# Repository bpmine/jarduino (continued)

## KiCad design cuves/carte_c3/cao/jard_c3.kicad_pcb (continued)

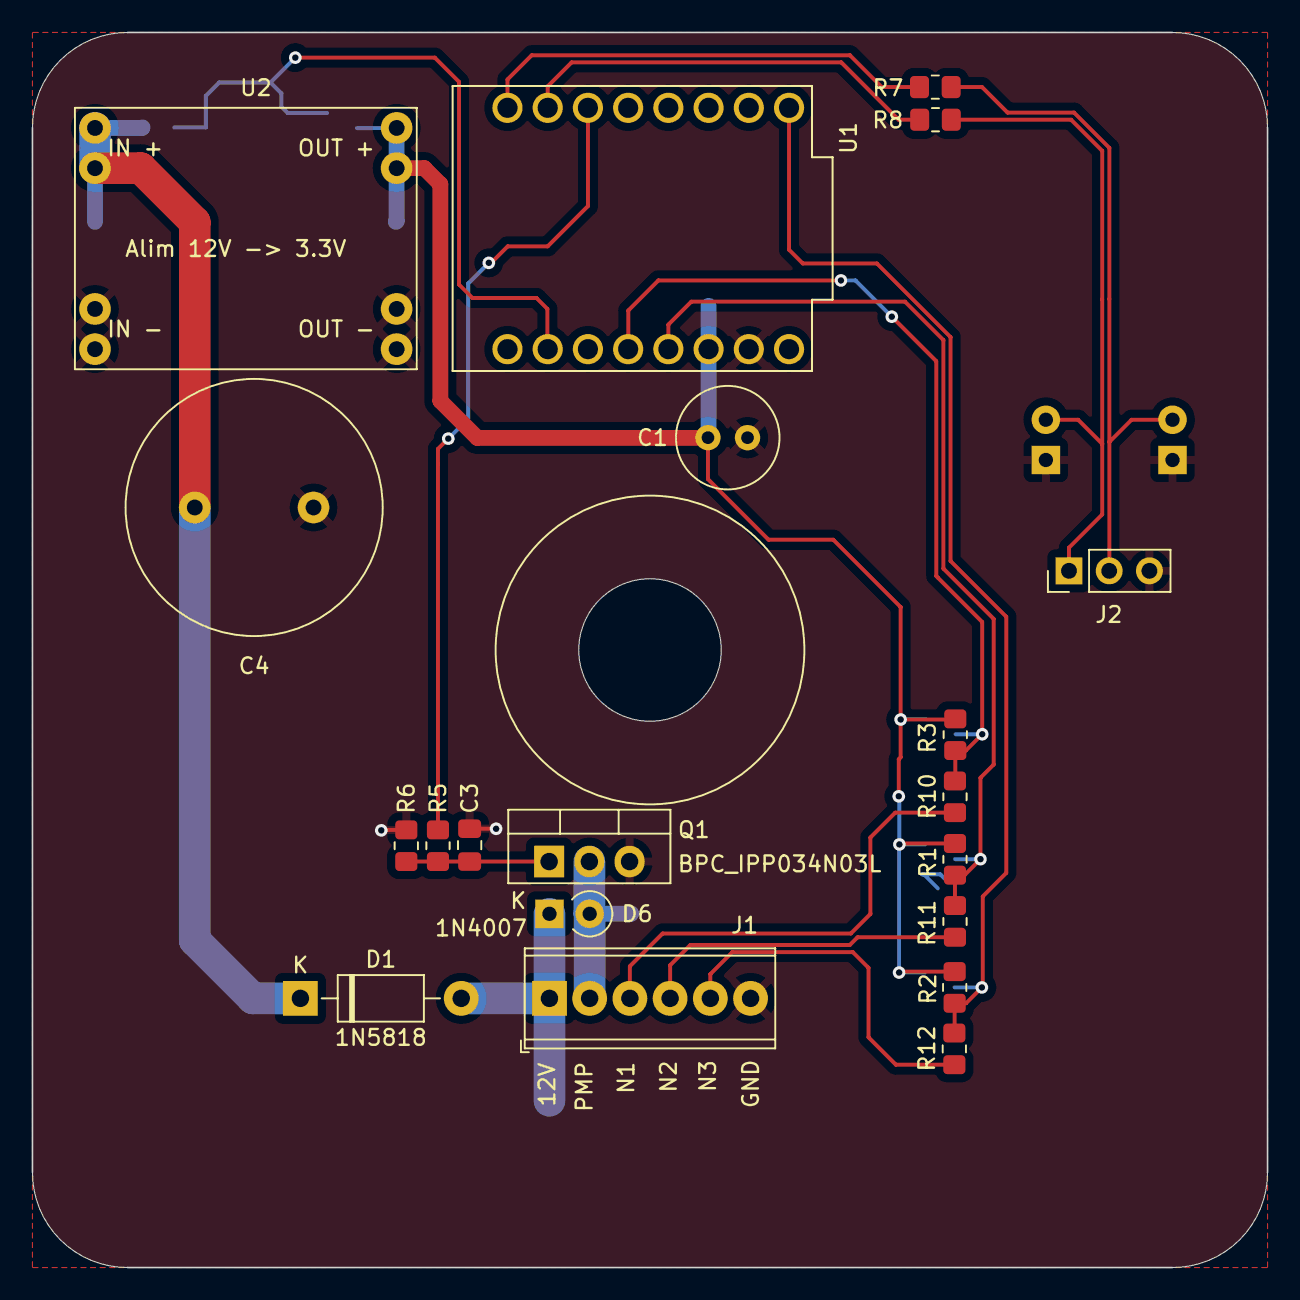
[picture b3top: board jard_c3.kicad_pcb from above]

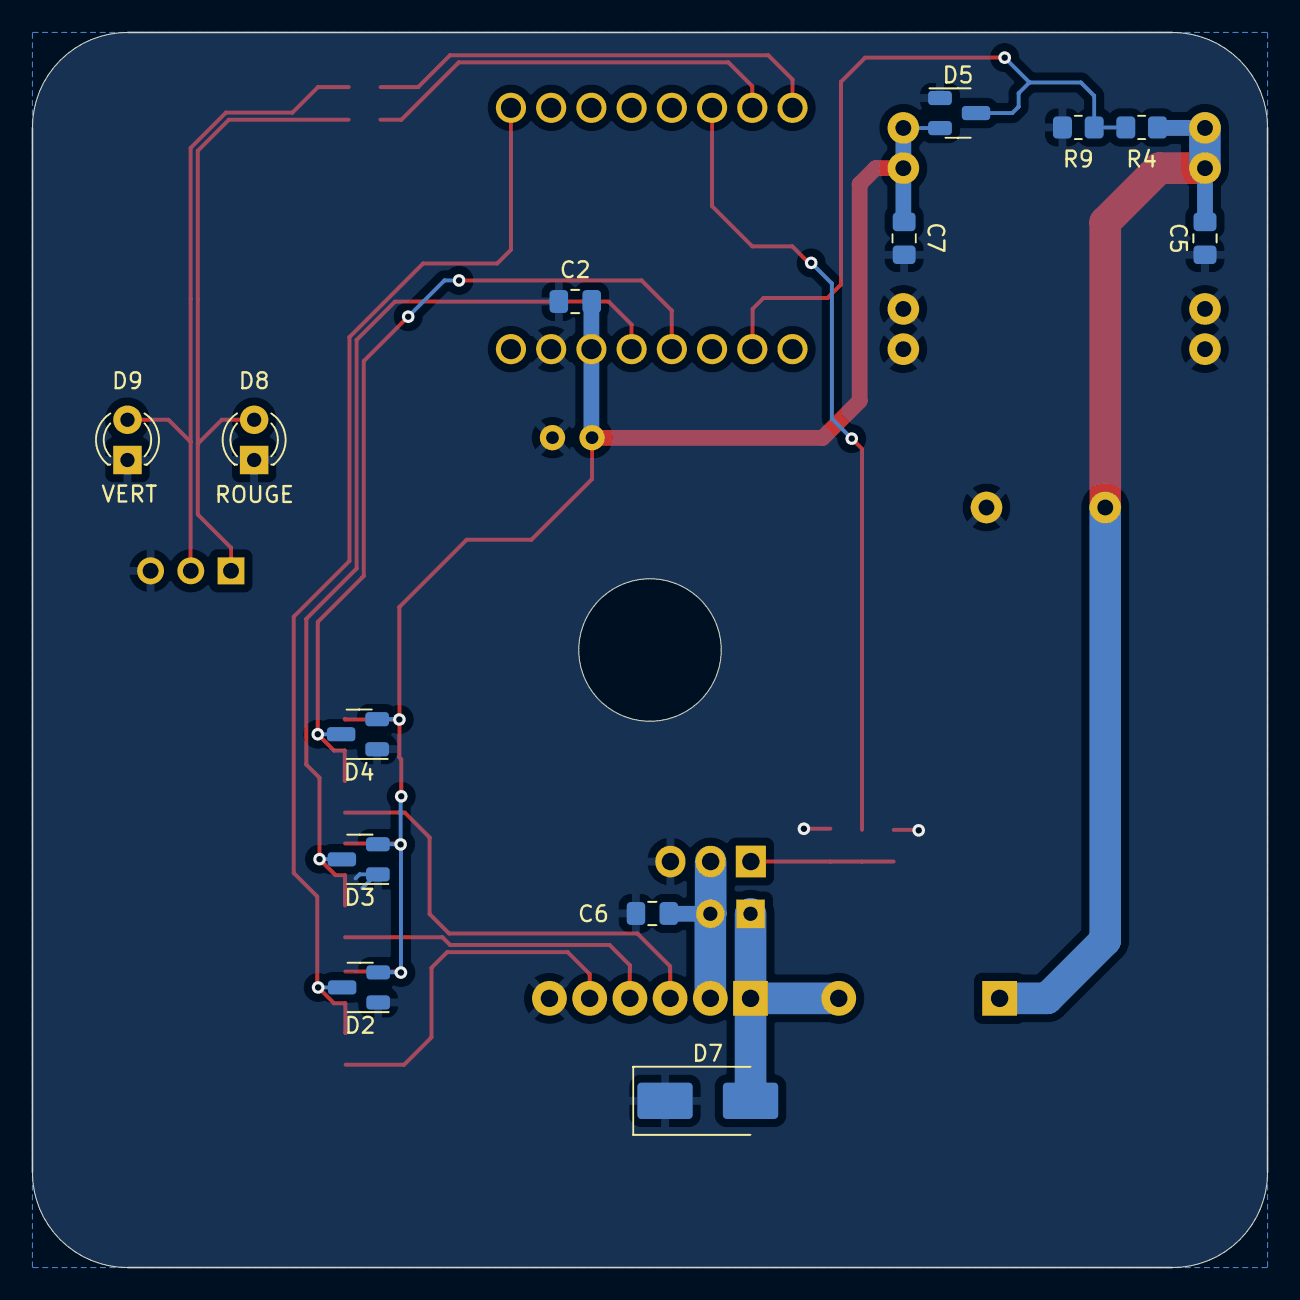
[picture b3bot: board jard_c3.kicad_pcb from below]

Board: 2 copper layers, 78.0 x 78.0 mm, 33 parts (13 on the bottom side), 18 nets.

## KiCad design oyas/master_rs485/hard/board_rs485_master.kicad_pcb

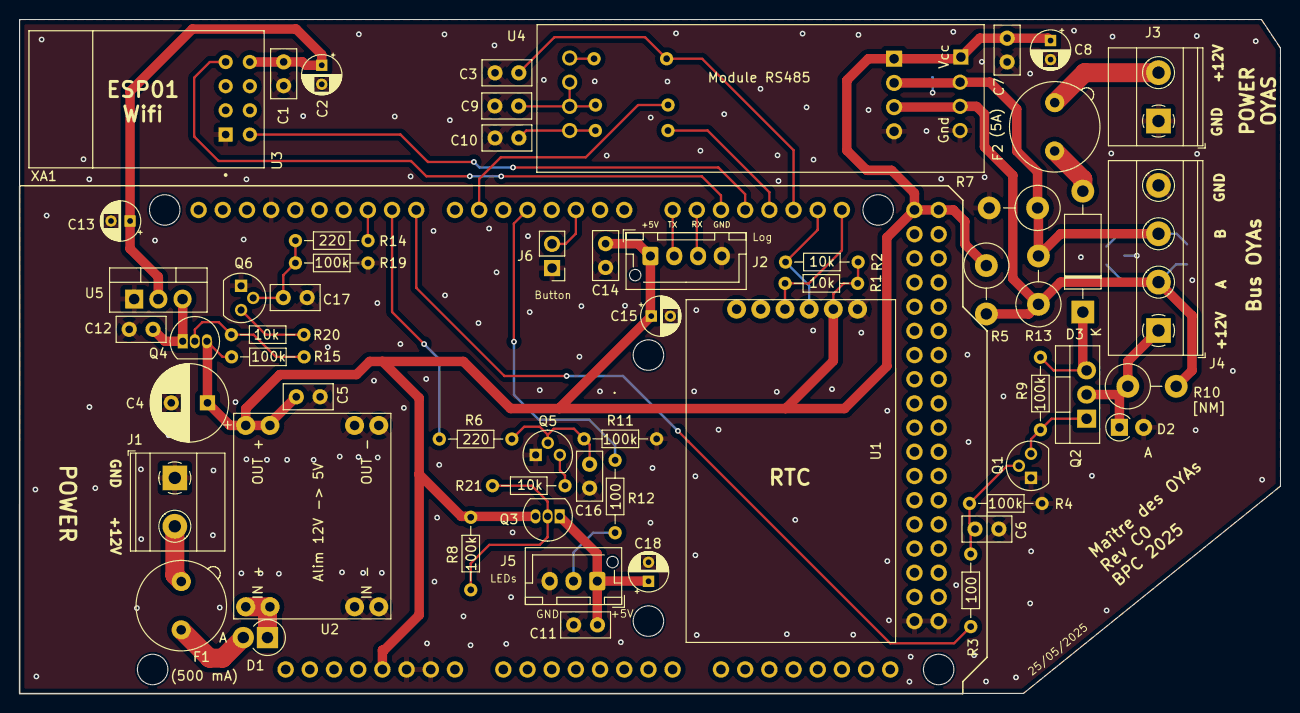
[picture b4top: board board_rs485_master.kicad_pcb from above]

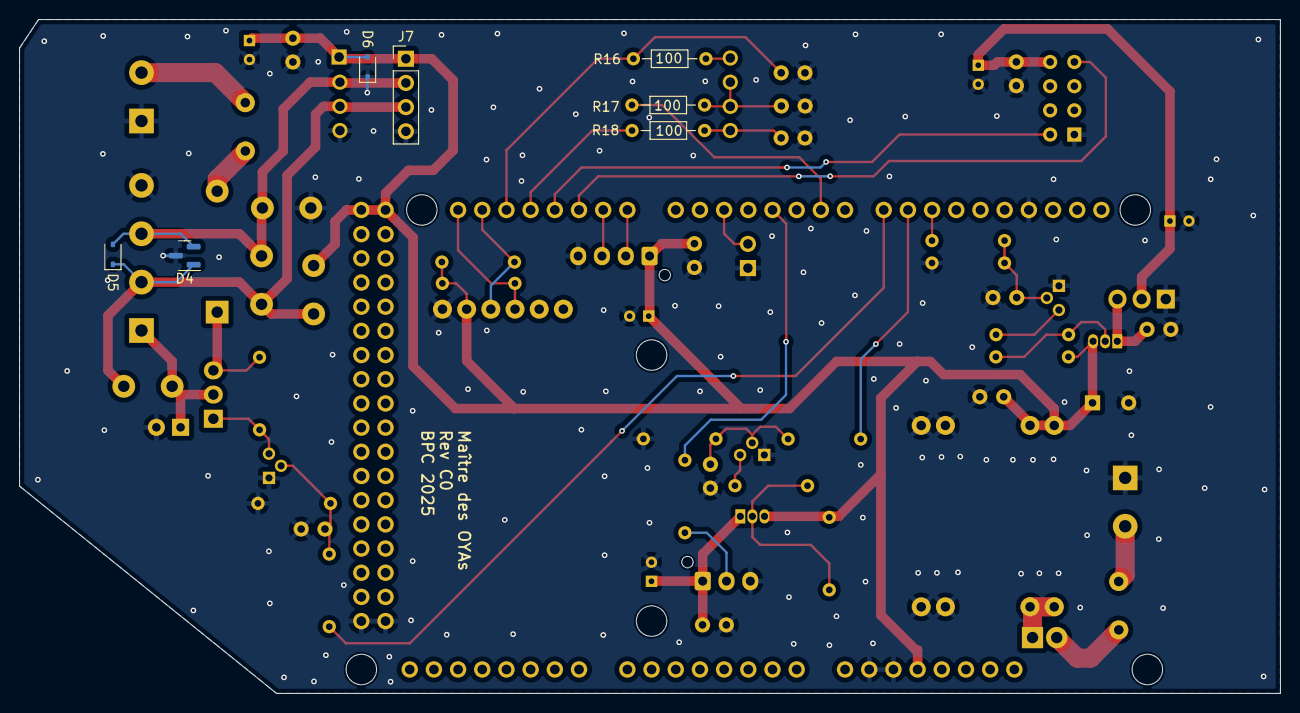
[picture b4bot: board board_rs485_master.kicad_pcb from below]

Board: 2 copper layers, 132.4 x 70.8 mm, 66 parts (7 on the bottom side), 40 nets.

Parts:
C1, C5, C6, C7, C11, C12, C14, C16, C17: 100nF; C_Disc_D5.0mm_W2.5mm_P2.50mm
C2, C8, C13, C15, C18: 10µF; CP_Radial_D4.0mm_P2.00mm
C3, C9, C10: 1nF; C_Disc_D5.0mm_W2.5mm_P2.50mm
C4: 100µF; CP_Radial_D8.0mm_P3.80mm
D1: SR560; D_DO-15_P2.54mm_Vertical_AnodeUp
D2: BAT42; D_A-405_P2.54mm_Vertical_AnodeUp
D3: SR560; D_DO-15_P12.70mm_Horizontal
D4: SM712_SOT23; SOT-23
D5, D6: SD12_SOD323; D_SOD-323
F1: 500 mA; Fuseholder_TR5_Littelfuse_No560_No460
F2: 5A; Fuseholder_TR5_Littelfuse_No560_No460
J1: POWER_12V; TerminalBlock_Phoenix_MKDS-1,5-2-5.08_1x02_P5.08mm_Horizont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
J2: Log; JST_XH_B4B-XH-AM_1x04_P2.50mm_Vertical
J3: POWER_OYAS_12V; TerminalBlock_Phoenix_MKDS-1,5-2-5.08_1x02_P5.08mm_Horizont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
J4: BUS_OYAS; TerminalBlock_Phoenix_MKDS-1,5-4-5.08_1x04_P5.08mm_Horizont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
J5: Leds RGB; JST_XH_B3B-XH-AM_1x03_P2.50mm_Vertical
J6: Button; PinHeader_1x02_P2.54mm_Vertical
J7: Adapt BUS; PinHeader_1x04_P2.54mm_Vertical
Q1, Q5, Q6: BPC_2N2222A; TO-92
Q2: P03P4L-04; TO-220-3_Vertical
Q3, Q4: BC327; TO-92_Inline
R1, R2, R20, R21: 10k; R_Axial_DIN0204_L3.6mm_D1.6mm_P7.62mm_Horizontal
R3, R12, R16, R17, R18: 100; R_Axial_DIN0204_L3.6mm_D1.6mm_P7.62mm_Horizontal
R4, R8, R9, R11, R15, R19: 100k; R_Axial_DIN0204_L3.6mm_D1.6mm_P7.62mm_Horizontal
R5, R7: 220; R_Axial_DIN0414_L11.9mm_D4.5mm_P5.08mm_Vertical
R6, R14: 220; R_Axial_DIN0204_L3.6mm_D1.6mm_P7.62mm_Horizontal
R10: R; R_Axial_DIN0414_L11.9mm_D4.5mm_P5.08mm_Vertical
R13: 128; R_Axial_DIN0414_L11.9mm_D4.5mm_P5.08mm_Vertical
U1: RtcArduino; BPC_RtcArduino
U2: BPC_Alim5V
U3: BPC_ESP8266-01_ESP-01; BPC_XCVR_ESP8266-01_ESP-01
U4: BPC_Mod485
U5: LM1117DT-3.3; TO-220-3_Vertical
XA1: Arduino_Mega2560_Shield; BPC_Arduino_Mega2560_Shield

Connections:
+5V: C4.1, C5.1, C7.1, C8.1, C14.1, C15.1, D6.2 (A2), J2.1, J7.1, Q3.3 (E), Q4.3 (E), R1.1, R2.1, R5.1, R8.1, R15.1, U1.2 (VCC), U2.7 (OUT+), U2.8 (OUT+), U4.1 (Vcc), XA1.5V1 (5V), XA1.5V3 (5V), XA1.5V4 (5V)
A: D4.1 (A1), D5.1 (A1), J4.2, J7.3, R5.2, R10.2, R13.1, U4.3 (A)
B: D4.2 (A2), D5.2 (A2), J4.3, J7.2, R7.1, R13.2, U4.2 (B)
CMD_LEDS_PWR: R6.1, XA1.D9
CMD_OYAS_PWR: R3.2, XA1.D8
CMD_WIFI_PWR: R14.1, XA1.D10
DATA_LEDS: R12.1, XA1.D4
GND: C1.2, C2.2, C3.2, C4.2, C5.2, C6.2, C7.2, C8.2, C9.2, C10.2, C11.2, C12.2, C13.2, C14.2, C15.2, C16.2, C17.2, C18.2, D2.2 (A), D4.3 (common), D6.1 (A1), J1.1, J2.4, J3.1, J4.4, J5.3, J6.1, J7.4, Q1.1, Q5.1, Q6.1, R4.2, R7.2, R11.2, R19.2, U1.1 (GND), U2.3 (IN-), U2.4 (IN-), U2.5 (OUT-), U2.6 (OUT-), U3.1 (GND), U4.4 (Gnd), U5.1 (GND), XA1.GND1 (GND), XA1.GND2 (GND), XA1.GND3 (GND), XA1.GND5 (GND), XA1.GND6 (GND)
unnamed: C6.1, Q1.2, R3.1, R4.1
unnamed: C16.1, Q5.2, R6.2, R11.1
unnamed: C17.1, Q6.2, R14.2, R19.1
unnamed: D1.2 (A), F1.1
unnamed: D1.1 (K), U2.1 (IN+), U2.2 (IN+)
unnamed: D2.1 (K), J4.1, Q2.2 (D), R10.1
unnamed: D3.2 (A), F2.1
unnamed: D3.1 (K), Q2.3 (S), R9.1
unnamed: F1.2, J1.2
unnamed: F2.2, J3.2
unnamed: C11.1, C18.1, J5.1, Q3.1 (C)
unnamed: J5.2, R12.2
unnamed: Q1.3, Q2.1 (G), R9.2
unnamed: Q3.2 (B), R8.2, R21.2
unnamed: Q4.2 (B), R15.2, R20.2
unnamed: C12.1, Q4.1 (C), U5.3 (VI)
unnamed: Q5.3, R21.1
unnamed: Q6.3, R20.1
unnamed: C9.1, R17.1, U4.6 (DE), U4.7 (RE)
unnamed: C10.1, R18.1, U4.5 (DI)
unnamed: R16.1, U4.8 (RO)
POWER_3.3: C1.1, C2.1, C13.1, U3.8 (VCC), U5.2 (VO)
RS485_RX: C3.1, R16.2, XA1.D19 (D19_RX1)
RS485_TX: R18.2, XA1.D18 (D18_TX1)
RX_LOG: J2.3, XA1.D15 (D15_RX3)
RX_WIFI: U3.5 (TXD), XA1.D17 (D17_RX2)
SCL: R1.2, U1.4 (SCL), XA1.D21 (D21_SCL)
SDA: R2.2, U1.3 (SDA), XA1.D20 (D20_SDA)
TEST_BTN: J6.2, XA1.D2 (D2_INT0)
TX_EN: R17.2, XA1.D6
TX_LOG: J2.2, XA1.D14 (D14_TX3)
TX_WIFI: U3.4 (RXD), XA1.D16 (D16_TX2)

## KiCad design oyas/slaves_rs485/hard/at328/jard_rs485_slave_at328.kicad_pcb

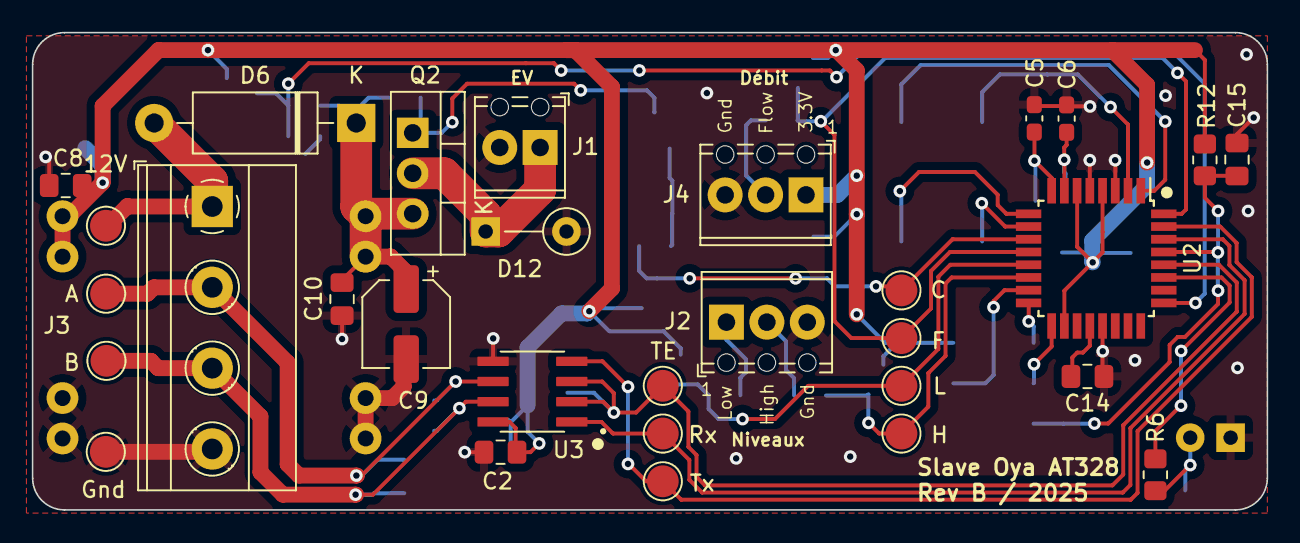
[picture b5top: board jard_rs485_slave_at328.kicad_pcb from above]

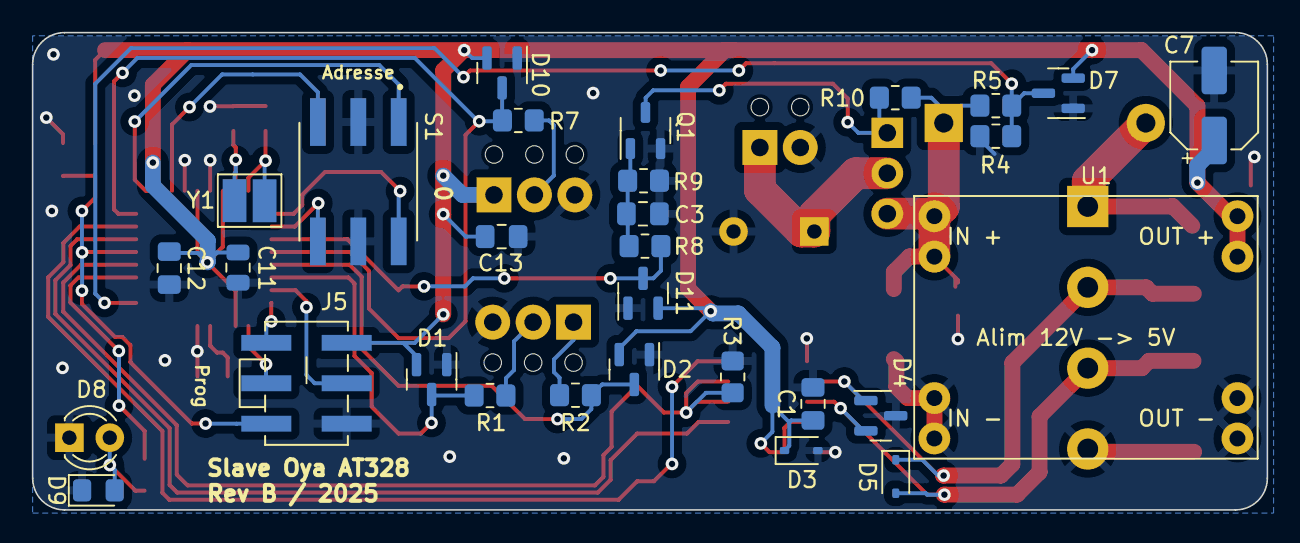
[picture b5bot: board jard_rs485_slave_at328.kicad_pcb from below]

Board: 2 copper layers, 77.6 x 30.0 mm, 60 parts (30 on the bottom side), 33 nets.

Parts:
C1: 10nF; C_0805_2012Metric_Pad1.18x1.45mm_HandSolder
C2, C3, C12, C13, C14, C15: 100nF; C_0805_2012Metric_Pad1.18x1.45mm_HandSolder
C5, C6: 6pF; C_0603_1608Metric_Pad1.08x0.95mm_HandSolder
C7, C9: 10µF; CP_Elec_5x5.9
C8, C10: 1nF; C_0805_2012Metric_Pad1.18x1.45mm_HandSolder
C11: 1nF; C_0805_2012Metric
D1, D2, D7, D10, D11: BAV99; SOT-23
D3, D5: SD12_SOD323; D_SOD-323
D4: SM712_SOT23; SOT-23
D6: SR560; D_DO-15_P12.70mm_Horizontal
D8: LED; LED_D3.0mm_FlatTop
D9: LED; LED_0805_2012Metric_Pad1.15x1.40mm_HandSolder
D12: 1N4007G; D_A-405_P5.08mm_Vertical_KathodeUp
J1: EV1; TerminalBlock_Phoenix_MPT-0,5-2-2.54_1x02_P2.54mm_Horizontal
J2: Niveaux; TerminalBlock_Phoenix_MPT-0,5-3-2.54_1x03_P2.54mm_Horizontal
J3: POWER; TerminalBlock_Phoenix_MKDS-1,5-4-5.08_1x04_P5.08mm_Horizont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
J4: Débit; TerminalBlock_Phoenix_MPT-0,5-3-2.54_1x03_P2.54mm_Horizontal
J5: ISCP; BPC_ISCP_CMS
Q1: BPC_FMMT38C; BPC_SOT-23-3
Q2: P03P4L-04; TO-220-3_Vertical
R1, R2, R7, R12: 100; R_0805_2012Metric_Pad1.20x1.40mm_HandSolder
R3, R5, R9, R10: 100k; R_0805_2012Metric_Pad1.20x1.40mm_HandSolder
R4: 40k; R_0805_2012Metric_Pad1.20x1.40mm_HandSolder
R6, R8: 220; R_0805_2012Metric_Pad1.20x1.40mm_HandSolder
S1: RDS-16S-74385-SMT; BPC_RDS-16S-74385-SMT
TP1: H; TestPoint_Pad_D2.0mm
TP2: L; TestPoint_Pad_D2.0mm
TP3: Rx; TestPoint_Pad_D2.0mm
TP4: Tx; TestPoint_Pad_D2.0mm
TP5: TE; TestPoint_Pad_D2.0mm
TP6: B; TestPoint_Pad_D2.0mm
TP7: A; TestPoint_Pad_D2.0mm
TP8: 12V; TestPoint_Pad_D2.0mm
TP9: Gnd; TestPoint_Pad_D2.0mm
TP10: F; TestPoint_Pad_D2.0mm
TP11: C; TestPoint_Pad_D2.0mm
U1: BPC_Alim5V
U2: ATmega328P-A; TQFP-32_7x7mm_P0.8mm
U3: MAX485E; BPC_MAX485E_SOIC127P600X175-8N
Y1: 8MHz; BPC_Quartz_8MHz

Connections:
+5V: C1.1, C2.2, C7.1, C8.1, C11.1, C12.1, C13.1, D1.2 (A), D2.2 (A), D3.1 (A1), D7.2 (A), D10.2 (A), D11.2 (A), J4.1, J5.2 (VCC), R12.2, U1.7 (OUT+), U1.8 (OUT+), U2.4 (VCC), U2.6 (VCC), U2.18 (AVCC), U3.8 (VCC)
A1: S1.1, U2.1 (PD3)
A2: S1.2, U2.10 (PD6)
A3: S1.4, U2.2 (PD4)
A4: S1.8, U2.9 (PD5)
BUS_A: D4.1 (A1), D5.1 (A1), J3.2, TP7.1, U3.6 (A)
BUS_B: D4.2 (A2), D5.2 (A2), J3.3, TP6.1, U3.7 (B)
CMD_EV1: D11.3 (K), R8.1, TP11.1, U2.11 (PD7)
FLOW: D10.3 (K), R7.2, TP10.1, U2.12 (PB0), U2.32 (PD2)
GND: C1.2, C2.1, C3.2, C5.2, C6.1, C7.2, C8.2, C9.2, C10.2, C11.2, C12.2, C13.2, C14.1, C15.2, D1.1 (K), D2.1 (K), D3.2 (A2), D4.3 (common), D7.1 (K), D8.1 (K), D9.1 (K), D10.1 (K), D11.1 (K), D12.2 (A), J1.2, J2.3, J3.4, J4.3, J5.6 (GND), Q1.2 (E), R3.2, R4.1, R9.2, S1.C_1 (C), S1.C_2 (C), TP9.1, U1.3 (IN-), U1.4 (IN-), U1.5 (OUT-), U1.6 (OUT-), U2.3 (GND), U2.5 (GND), U2.21 (GND), U3.5 (GND)
LED: R6.1, U2.27 (PC4)
LVL_HIGH: D1.3 (K), R1.2, TP1.1, U2.14 (PB2)
LVL_LOW: D2.3 (K), R2.2, TP2.1, U2.13 (PB1)
MISO: J5.1 (MISO), U2.16 (PB4)
MOSI: J5.4 (MOSI), U2.15 (PB3)
unnamed: D6.2 (A), J3.1, TP8.1
unnamed: D8.2 (A), D9.2 (A), R6.2
unnamed: D12.1 (K), J1.1, Q2.2 (D)
unnamed: J2.1, R2.1
unnamed: J2.2, R1.1
unnamed: J4.2, R7.1
unnamed: C3.1, Q1.1 (B), R8.2, R9.1
unnamed: Q1.3 (C), Q2.1 (G), R10.2
unnamed: C14.2, U2.20 (AREF)
unnamed: C6.2, U2.7 (XTAL1/PB6), Y1.2
unnamed: C5.1, U2.8 (XTAL2/PB7), Y1.1
POWER_12V: C9.1, C10.1, D6.1 (K), Q2.3 (S), R5.2, R10.1, U1.1 (IN+), U1.2 (IN+)
POW_MES: D7.3 (K), R4.2, R5.1, U2.25 (PC2)
RESET: C15.1, J5.5 (RST), R12.1, U2.29 (~RESET/PC6)
RX: TP3.1, U2.30 (PD0), U3.1 (RO)
SCK: J5.3 (SCK), U2.17 (PB5)
TX: TP4.1, U2.31 (PD1), U3.4 (DI)
TX_EN: R3.1, TP5.1, U2.28 (PC5), U3.2 (~RE), U3.3 (DE)

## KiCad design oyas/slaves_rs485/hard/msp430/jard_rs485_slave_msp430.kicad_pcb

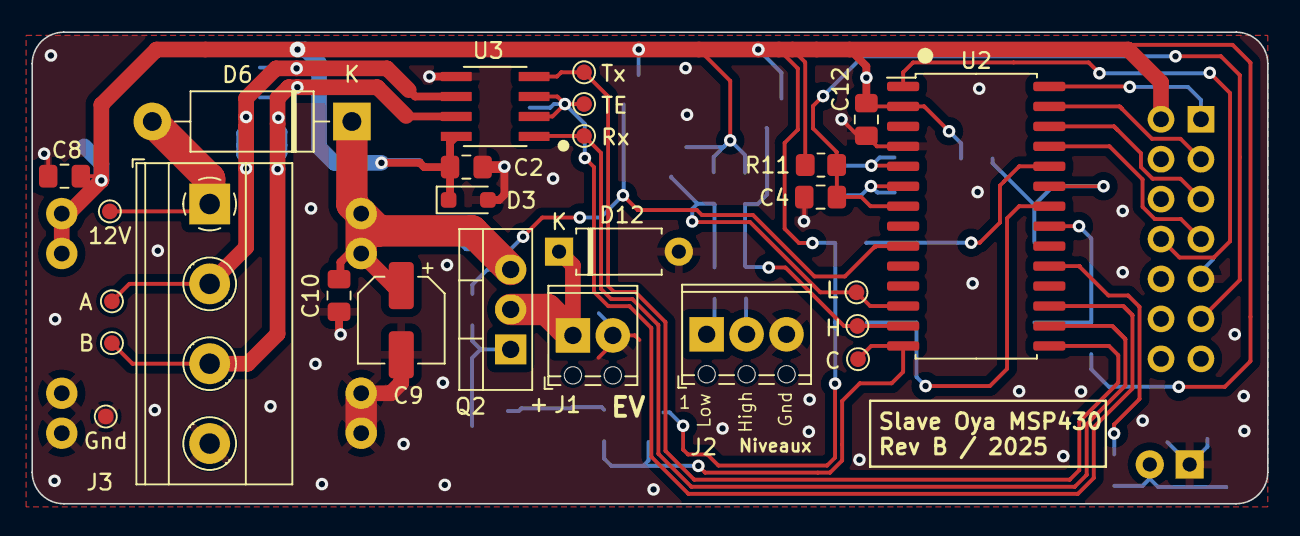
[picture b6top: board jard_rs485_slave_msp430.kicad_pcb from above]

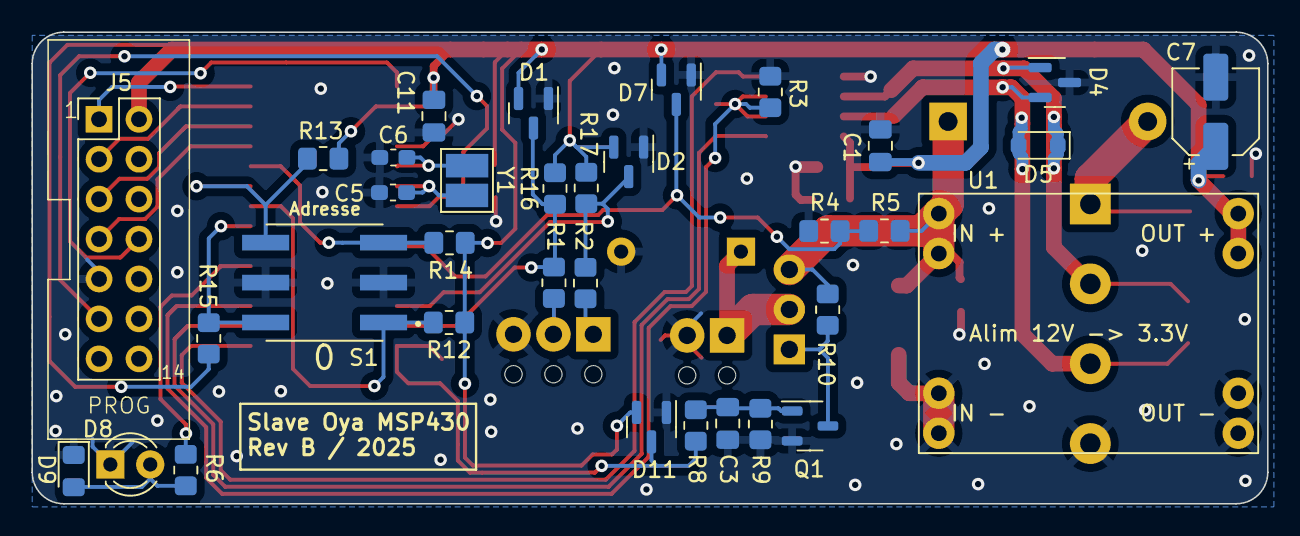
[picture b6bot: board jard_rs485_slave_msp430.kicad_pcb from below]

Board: 2 copper layers, 78.6 x 30.0 mm, 60 parts (34 on the bottom side), 32 nets.

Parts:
C1: 10µF; C_0805_2012Metric_Pad1.18x1.45mm_HandSolder
C2, C3, C12: 100nF; C_0805_2012Metric_Pad1.18x1.45mm_HandSolder
C4, C8, C10, C11: 1nF; C_0805_2012Metric_Pad1.18x1.45mm_HandSolder
C5, C6: 10pF; C_0603_1608Metric_Pad1.08x0.95mm_HandSolder
C7, C9: 10µF; CP_Elec_5x5.9
D1, D2, D7, D11: BAV99; SOT-23
D3, D5: SD12_SOD323; BPC_D_SOD-323_HandSoldering
D4: SM712_SOT23; SOT-23
D6: SR560; D_DO-15_P12.70mm_Horizontal
D8: LED; LED_D3.0mm_FlatTop
D9: LED; LED_0805_2012Metric_Pad1.15x1.40mm_HandSolder
D12: 1N4007G; D_A-405_P7.62mm_Horizontal
J1: EV1; TerminalBlock_Phoenix_MPT-0,5-2-2.54_1x02_P2.54mm_Horizontal
J2: Niveaux; TerminalBlock_Phoenix_MPT-0,5-3-2.54_1x03_P2.54mm_Horizontal
J3: POWER; TerminalBlock_Phoenix_MKDS-1,5-4-5.08_1x04_P5.08mm_Horizont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
J5: Prog MSP; BPC_PROG_MSP
Q1: BPC_FMMT38C; BPC_SOT-23-3
Q2: P03P4L-04; TO-220-3_Vertical
R1, R2: 100; R_0805_2012Metric_Pad1.20x1.40mm_HandSolder
R3, R5, R9, R10, R11, R12, R13, R14, R15, R16, R17: 100k; R_0805_2012Metric_Pad1.20x1.40mm_HandSolder
R4: 40k; R_0805_2012Metric_Pad1.20x1.40mm_HandSolder
R6, R8: 220; R_0805_2012Metric_Pad1.20x1.40mm_HandSolder
S1: RDS-16S-74385-SMT; BPC_RDS-16S-74385-SMT
TP1: H; TestPoint_Pad_D1.0mm
TP2: L; TestPoint_Pad_D1.0mm
TP3: Rx; TestPoint_Pad_D1.0mm
TP4: Tx; TestPoint_Pad_D1.0mm
TP5: TE; TestPoint_Pad_D1.0mm
TP6: B; TestPoint_Pad_D1.0mm
TP7: A; TestPoint_Pad_D1.0mm
TP8: 12V; TestPoint_Pad_D1.0mm
TP9: Gnd; TestPoint_Pad_D1.0mm
TP11: C; TestPoint_Pad_D1.0mm
U1: BPC_Alim3_3V
U2: MSP430F1232IDW; SOIC-28W_7.5x17.9mm_P1.27mm
U3: MAX485E; BPC_MAX485E_SOIC127P600X175-8N
Y1: 8MHz; BPC_Quartz_8MHz

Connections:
+3.3V: C1.1, C2.2, C7.1, C8.1, C11.2, C12.2, D1.2 (A), D2.2 (A), D3.1 (A1), D7.2 (A), D11.2 (A), J5.2 (Vcc), R11.2, R12.2, R13.2, R14.2, R15.2, R16.2, R17.2, U1.7 (OUT+), U1.8 (OUT+), U2.2 (VCC), U3.8 (VCC)
A1: R12.1, S1.1, U2.22 (TA0/P1.1)
A2: R13.1, S1.2, U2.23 (TA1/P1.2)
A3: R14.1, S1.4, U2.24 (TA2/P1.3)
A4: R15.1, S1.8, U2.21 (TACLK/ADC10CLK/P1.0)
BUS_A: D4.1 (A1), D5.1 (A1), J3.2, TP7.1, U3.6 (A)
BUS_B: D4.2 (A2), D5.2 (A2), J3.3, TP6.1, U3.7 (B)
CMD_EV1: D11.3 (K), R8.1, TP11.1, U2.14 (P3.3/UCLK0)
GND: C1.2, C2.1, C3.2, C4.2, C5.1, C6.1, C7.2, C8.2, C9.2, C10.2, C11.1, C12.1, D1.1 (K), D2.1 (K), D3.2 (A2), D4.3 (common), D7.1 (K), D8.1 (K), D9.1 (K), D11.1 (K), D12.2 (A), J1.2, J2.3, J3.4, J5.9 (GND), Q1.2 (E), R3.2, R4.1, R9.2, S1.C_1 (C), S1.C_2 (C), TP9.1, U1.3 (IN-), U1.4 (IN-), U1.5 (OUT-), U1.6 (OUT-), U2.4 (VSS), U3.5 (GND)
LED: R6.1, U2.19 (TA1/VeREF-/VREF-/A3/P2.3)
LVL_HIGH: D1.3 (K), R1.2, R16.1, TP1.1, U2.13 (P3.2/SOMI0)
LVL_LOW: D2.3 (K), R2.2, R17.1, TP2.1, U2.12 (P3.1/SIMO0)
unnamed: D6.2 (A), J3.1, TP8.1
unnamed: D8.2 (A), D9.2 (A), R6.2
unnamed: D12.1 (K), J1.1, Q2.2 (D)
unnamed: J2.1, R2.1
unnamed: J2.2, R1.1
unnamed: C4.1, J5.11 (RST), R11.1, U2.7 (~RST/NMI)
unnamed: C3.1, Q1.1 (B), R8.2, R9.1
unnamed: Q1.3 (C), Q2.1 (G), R10.2
unnamed: C5.2, U2.6 (XIN), Y1.2
unnamed: C6.2, U2.5 (XOUT), Y1.1
POWER_12V: C9.1, C10.1, D6.1 (K), Q2.3 (S), R5.2, R10.1, U1.1 (IN+), U1.2 (IN+)
POW_MES: D7.3 (K), R4.2, R5.1, U2.9 (INCLK/A1/P2.1)
RX: TP3.1, U2.16 (P3.5/URXD0), U3.1 (RO)
TCK: J5.7 (TCK), U2.25 (SMCLK/TCK/P1.4)
TDI: J5.3 (TDI), U2.27 (TDI/TCLK/TA1/P1.6)
TDO: J5.1 (TDO), U2.28 (TDO/TDI/TA2/P1.7)
TEST: J5.8 (TEST), U2.1 (TEST)
TMS: J5.5 (TMS), U2.26 (TMS/TA0/P1.5)
TX: TP4.1, U2.15 (P3.4/UTXD0), U3.4 (DI)
TX_EN: R3.1, TP5.1, U2.17 (P3.6/A6), U3.2 (~RE), U3.3 (DE)

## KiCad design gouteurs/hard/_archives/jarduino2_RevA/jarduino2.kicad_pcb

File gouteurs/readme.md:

# Goutteurs (Jarduino2)

Jarduino2 est une évolution du premier jarduino fabriqué en 2019.

Le premier jarduino était construit avec des platines de prototypage et un arduino MKR Zero Wifi.

Ce nouveau jarduino est construit à partir d'un Nano. On peut le configurer à l'aide d'une interface MODBUS sur l'USB ou bien sur le port série d'extension.
Il est possible de lui ajouter une extension Wifi pour le relier au réseau.

## Vue d'ensemble

Deux systèmes jarduinos étaient actifs en 2024, couvrant deux zones de jardin.
Chaque système est alimenté par une cuve à l'aide d'une pompe ou deux pompes.

Un coffret de commande permet de mettre ou non en service le système et de déclencher un arrosage en mode manuel.

Chaque coffret peut se programmer à l'aide d'un logiciel PC connecté à l'USB de la carte de commande. Cela permet d'activer ou non le mode automatique et de choisir l'heure de déclenchement et la durée d'arrosage.

Le coffret dispose de deux sorties pouvant commander deux pompes. Chaque voie peut alimenter jusqu'à 20 goutteurs. 

## Hardware

### Caractéristiques

  - Alimentation 12V;
  - Entrée de mesure de tension de panneau solaire;
  - 2 sorties 5W pour pompe (De type aquarium);
  - Sonde de température/Humidité;
  - LEDs et interrupteurs.

### Schéma

## Logiciels

### Logiciel embarqué dans la carte de commande
[Logiciel gestion des goutteurs](./src)

### Logiciel PC pour configurer le système

## Protocole MODBUS

Le jarduino implémente un serveur/esclave MODBUS.

Seules les functions suivantes sont implémentées:

- 01 READ COIL STATUS
- 02 READ INPUT STATUS
- 03 READ HOLDING REGISTERS
- 04 READ INPUT REGISTERS
- 15 WRITE MULTIPLE COILS
- 16 WRITE MULTIPLE REGISTERS

### Table des COILs (Lecture/Ecriture)

Adresse | Description
--- | ---
10 | Forçage POMPE 1
11 | Autorisation/Activation POMPE 1
12 | Mode automatique POMPE 1
13 | Mode Distant POMPE 1
14 | Commande distante POMPE 1
--- | ---
20 | Forçage POMPE 2
21 | Autorisation/Activation POMPE 2
22 | Mode automatique POMPE 2
23 | Mode Distant POMPE 2
24 | Commande distante POMPE 2

Ces bits sont enregistrés en EEPROM sauf ceux qui correspondent au forçage des pompes et à leur commande distante.

NB: La commande à distance des pompe est appliquée seulement si le maître modbus communique toujours avec le jarduino nano.

### Table des Entrees (Lecture)

Adresse | Description
--- | ---
0 | Etat LED pompe 1
1 | Etat LED pompe 2
2 | Tension battery OK
3 | Tension panneau solaire OK
4 | Est en mode veille

### Table des INPUT REGISTERs (Lecture)

Adresse | Description
--- | ---
0 | Niveau de batterie en dxV
1 | Niveau du panneau solaire en dxV
2 | Temperature en °C
3 | Humidité en %
4 | Temps restant avant détection Comm perdue (en ms)
5 | Temps restant avant veille (en ms)
--- | ---
10 | Temps restant timer de pompe 1 (en min)
--- | ---
20 | Temps restant timer de pompe 2 (en min)
--- | ---
100 | Nombre total de boots
101 | Temps de fonctionnement total POMPE 1 (en H)
102 | Temps de fonctionnement total POMPE 1 (en H)
103 | Temps total d'ensoleillement (en H)
104 | Nombre total de pressions sur le bouton POMPE 1
104 | Nombre total de pressions sur le bouton POMPE 2
--- | ---
200 | Version (2 pour jarduino 2)
201 | Numéro de série du Jarduino
202 | Version du logiciel nano

### Table des HOLDING REGISTERs (Lecture/Ecriture)

Adresse | Description
--- | ---
0 | Année
1 | Mois
2 | Jour
3 | Heure
4 | Minute
5 | Seconde
--- | ---
10 | Heure de démarrage POMPE 1
11 | Minute de démarrage POMPE 1
12 | Durée (en min) d'activation de la POMPE 1
13 | Jours de la semaine pour l'activation de la POMPE 1 (Bit 0: Dimanche, Bit 1: Lundi, ..., Bit 7: Samedi)
14 | Réglage du délai du timer de pompe 1 (en min)
--- | ---
20 | Heure de démarrage POMPE 2
21 | Minute de démarrage POMPE 2
22 | Durée (en min) d'activation de la POMPE 2
23 | Jours de la semaine pour l'activation de la POMPE 2 (Bit 0: Dimanche, Bit 1: Lundi, ..., Bit 7: Samedi)
24 | Réglage du délai du timer de pompe 2 (en min)

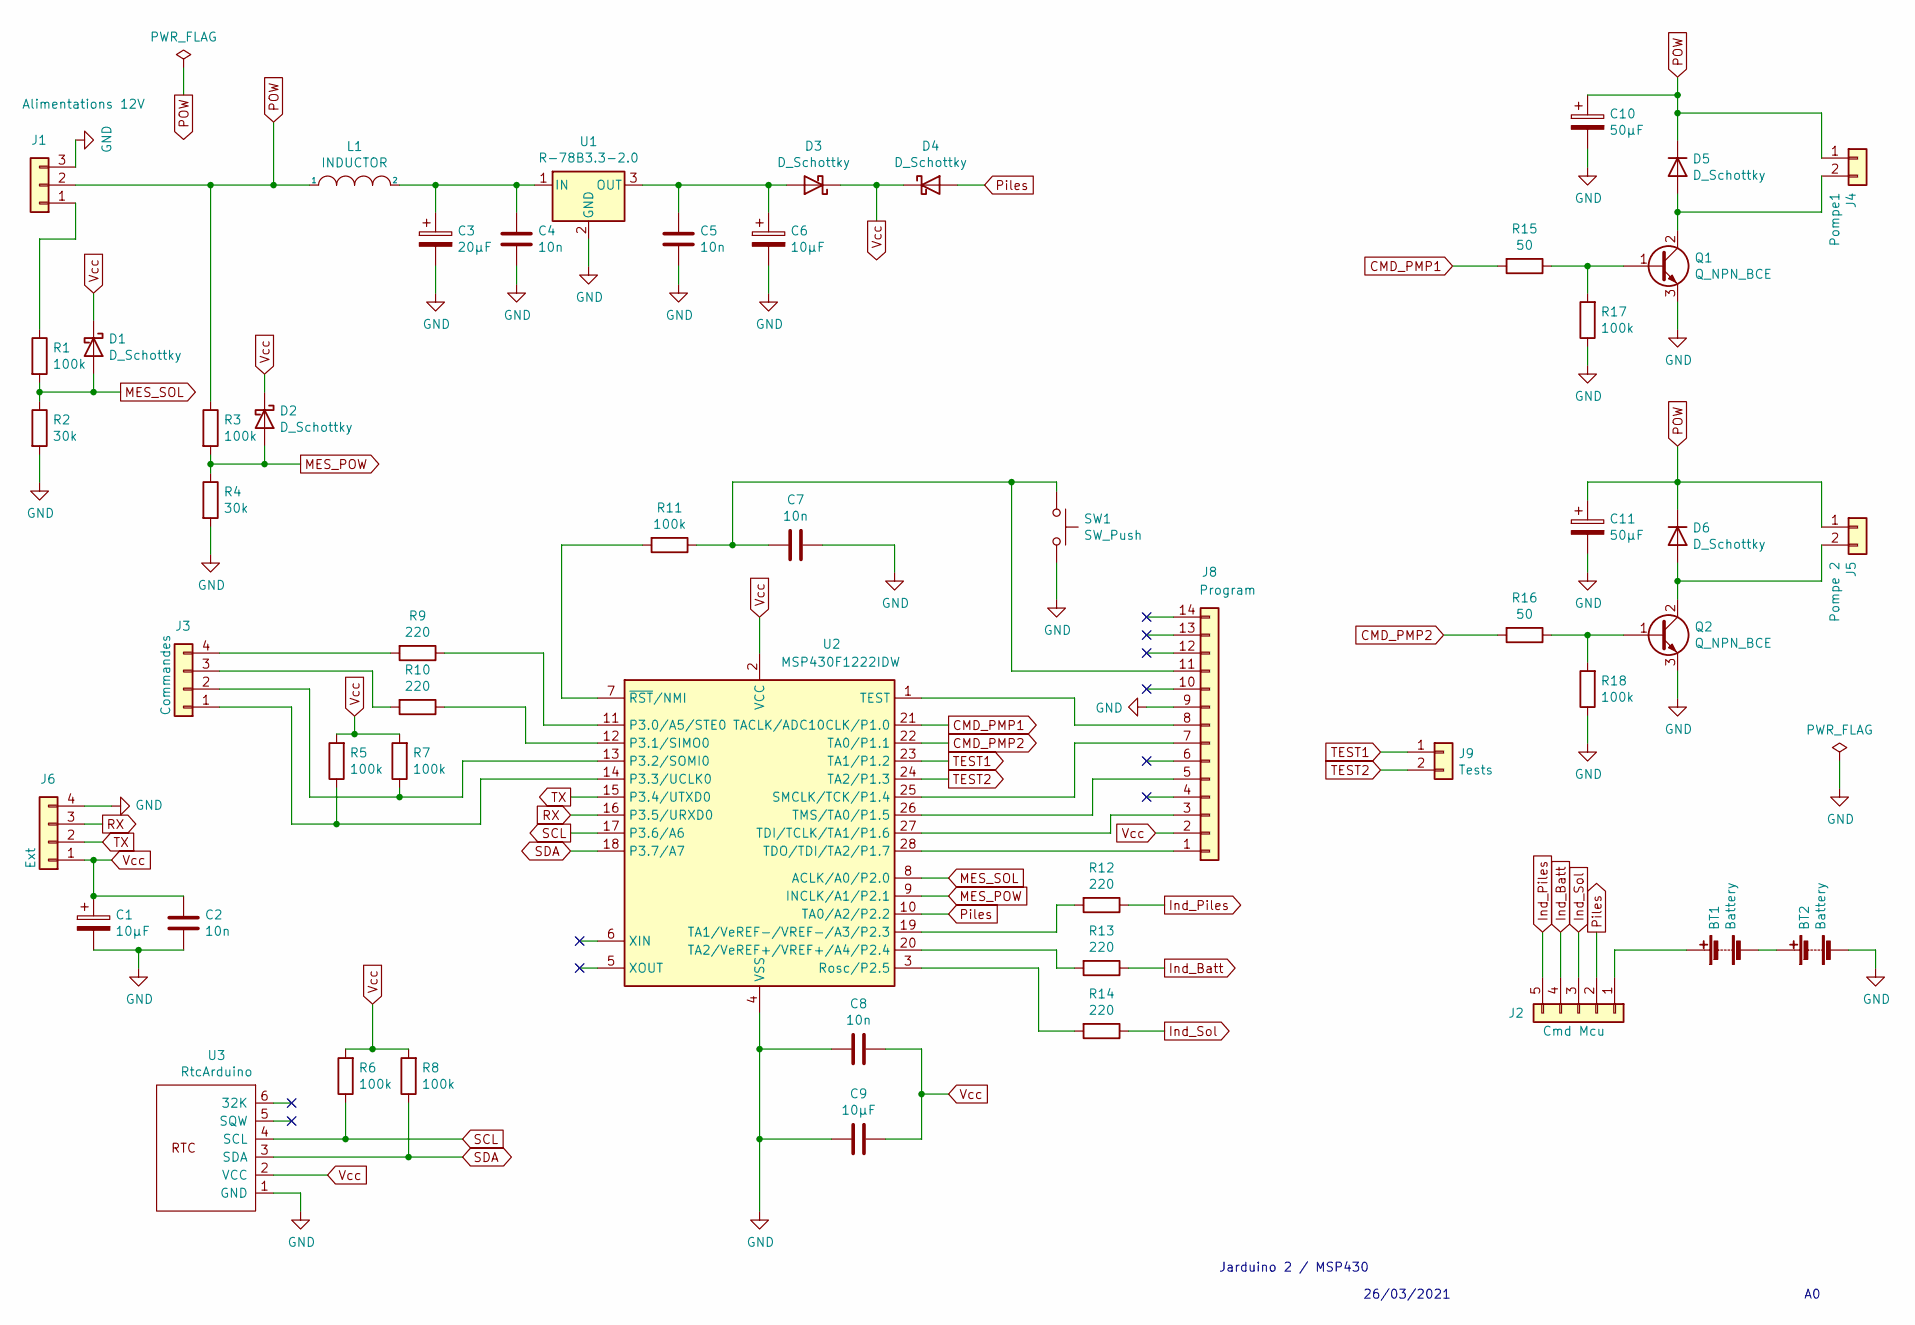
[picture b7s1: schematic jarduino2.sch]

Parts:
BT1, BT2: Battery; BatteryHolder_Keystone_2460_1xAA
C1, C6, C9: 10µF; C_1206_3216Metric
C2, C4, C5, C7, C8: 10n; C_0805_2012Metric
C3: 20µF; CP_Elec_6.3x7.7
C10, C11: 50µF; CP_Elec_8x6.5
D1, D2, D3, D4, D5, D6: D_Schottky; D_SOD-323
J1: Alimentations 12V; JST_GH_BM03B-GHS-TBT_1x03-1MP_P1.25mm_Vertical
J2: Cmd Mcu; JST_GH_BM05B-GHS-TBT_1x05-1MP_P1.25mm_Vertical
J3: Commandes; JST_GH_BM04B-GHS-TBT_1x04-1MP_P1.25mm_Vertical
J4: Pompe1; JST_GH_BM02B-GHS-TBT_1x02-1MP_P1.25mm_Vertical
J5: Pompe 2; JST_GH_BM02B-GHS-TBT_1x02-1MP_P1.25mm_Vertical
J6: Ext; JST_GH_BM04B-GHS-TBT_1x04-1MP_P1.25mm_Vertical
J8: Program; PinHeader_2x07_P2.54mm_Vertical_SMD
J9: Tests; PinHeader_1x02_P2.54mm_Vertical_SMD_Pin1Left
L1: INDUCTOR; L_1206_3216Metric
Q1, Q2: Q_NPN_BCE; SC-59_Handsoldering
R1, R3, R5, R6, R7, R8, R11, R17, R18: 100k; R_0805_2012Metric_Pad1.20x1.40mm_HandSolder
R2, R4: 30k; R_0805_2012Metric_Pad1.20x1.40mm_HandSolder
R9, R10, R12, R13, R14: 220; R_0805_2012Metric_Pad1.20x1.40mm_HandSolder
R15, R16: 50; R_0805_2012Metric_Pad1.20x1.40mm_HandSolder
SW1: SW_Push; Panasonic_EVQPUJ_EVQPUA
U1: R-78B3.3-2.0; SC-59
U2: MSP430F1222IDW; SOIC-28W_7.5x17.9mm_P1.27mm
U3: RtcArduino; BPC_RtcArduino

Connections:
CMD_PMP1: R15.2, U2.21 (TACLK/ADC10CLK/P1.0)
CMD_PMP2: R16.2, U2.22 (TA0/P1.1)
GND: BT2.2 (-), C1.2, C2.1, C3.2, C4.1, C5.1, C6.2, C7.1, C8.2, C9.2, C10.2, C11.2, J1.3, J6.4, J8.9, Q1.3 (E), Q2.3 (E), R2.2, R4.2, R17.1, R18.1, SW1.2, U1.2 (GND), U2.4 (VSS), U3.1 (GND)
Ind_Batt: J2.4, R13.1
Ind_Piles: J2.5, R12.1
Ind_Sol: J2.3, R14.1
MES_POW: D2.2 (A), R3.2, R4.1, U2.9 (INCLK/A1/P2.1)
MES_SOL: D1.2 (A), R1.2, R2.1, U2.8 (ACLK/A0/P2.0)
unnamed: BT1.1 (+), J2.1
unnamed: BT1.2 (-), BT2.1 (+)
unnamed: C3.1, C4.2, L1.2, U1.1 (IN)
unnamed: C5.2, C6.1, D3.2 (A), U1.3 (OUT)
unnamed: C7.2, J8.11, R11.1, SW1.1
unnamed: D5.2 (A), J4.2, Q1.2 (C)
unnamed: D6.2 (A), J5.2, Q2.2 (C)
unnamed: J1.1, R1.1
unnamed: J3.1, R5.1, U2.14 (P3.3/UCLK0)
unnamed: J3.2, R7.1, U2.13 (P3.2/SOMI0)
unnamed: J3.3, R10.2
unnamed: J3.4, R9.2
unnamed: J8.1, U2.28 (TDO/TDI/TA2/P1.7)
unnamed: J8.3, U2.27 (TDI/TCLK/TA1/P1.6)
unnamed: J8.5, U2.26 (TMS/TA0/P1.5)
unnamed: J8.7, U2.25 (SMCLK/TCK/P1.4)
unnamed: J8.8, U2.1 (TEST)
unnamed: Q1.1 (B), R15.1, R17.2
unnamed: Q2.1 (B), R16.1, R18.2
unnamed: R9.1, U2.11 (P3.0/A5/STE0)
unnamed: R10.1, U2.12 (P3.1/SIMO0)
unnamed: R11.2, U2.7 (~RST~/NMI)
unnamed: R12.2, U2.19 (TA1/VeREF-/VREF-/A3/P2.3)
unnamed: R13.2, U2.20 (TA2/VeREF+/VREF+/A4/P2.4)
unnamed: R14.2, U2.3 (Rosc/P2.5)
POW: C10.1, C11.1, D5.1 (K), D6.1 (K), J1.2, J4.1, J5.1, L1.1, R3.1
Piles: D4.2 (A), J2.2, U2.10 (TA0/A2/P2.2)
RX: J6.3, U2.16 (P3.5/URXD0)
SCL: R6.1, U2.17 (P3.6/A6), U3.4 (SCL)
SDA: R8.1, U2.18 (P3.7/A7), U3.3 (SDA)
TEST1: J9.1, U2.23 (TA1/P1.2)
TEST2: J9.2, U2.24 (TA2/P1.3)
TX: J6.2, U2.15 (P3.4/UTXD0)
Vcc: C1.1, C2.2, C8.1, C9.1, D1.1 (K), D2.1 (K), D3.1 (K), D4.1 (K), J6.1, J8.2, R5.2, R6.2, R7.2, R8.2, U2.2 (VCC), U3.2 (VCC)

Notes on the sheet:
Jarduino 2 / MSP430
26/03/2021

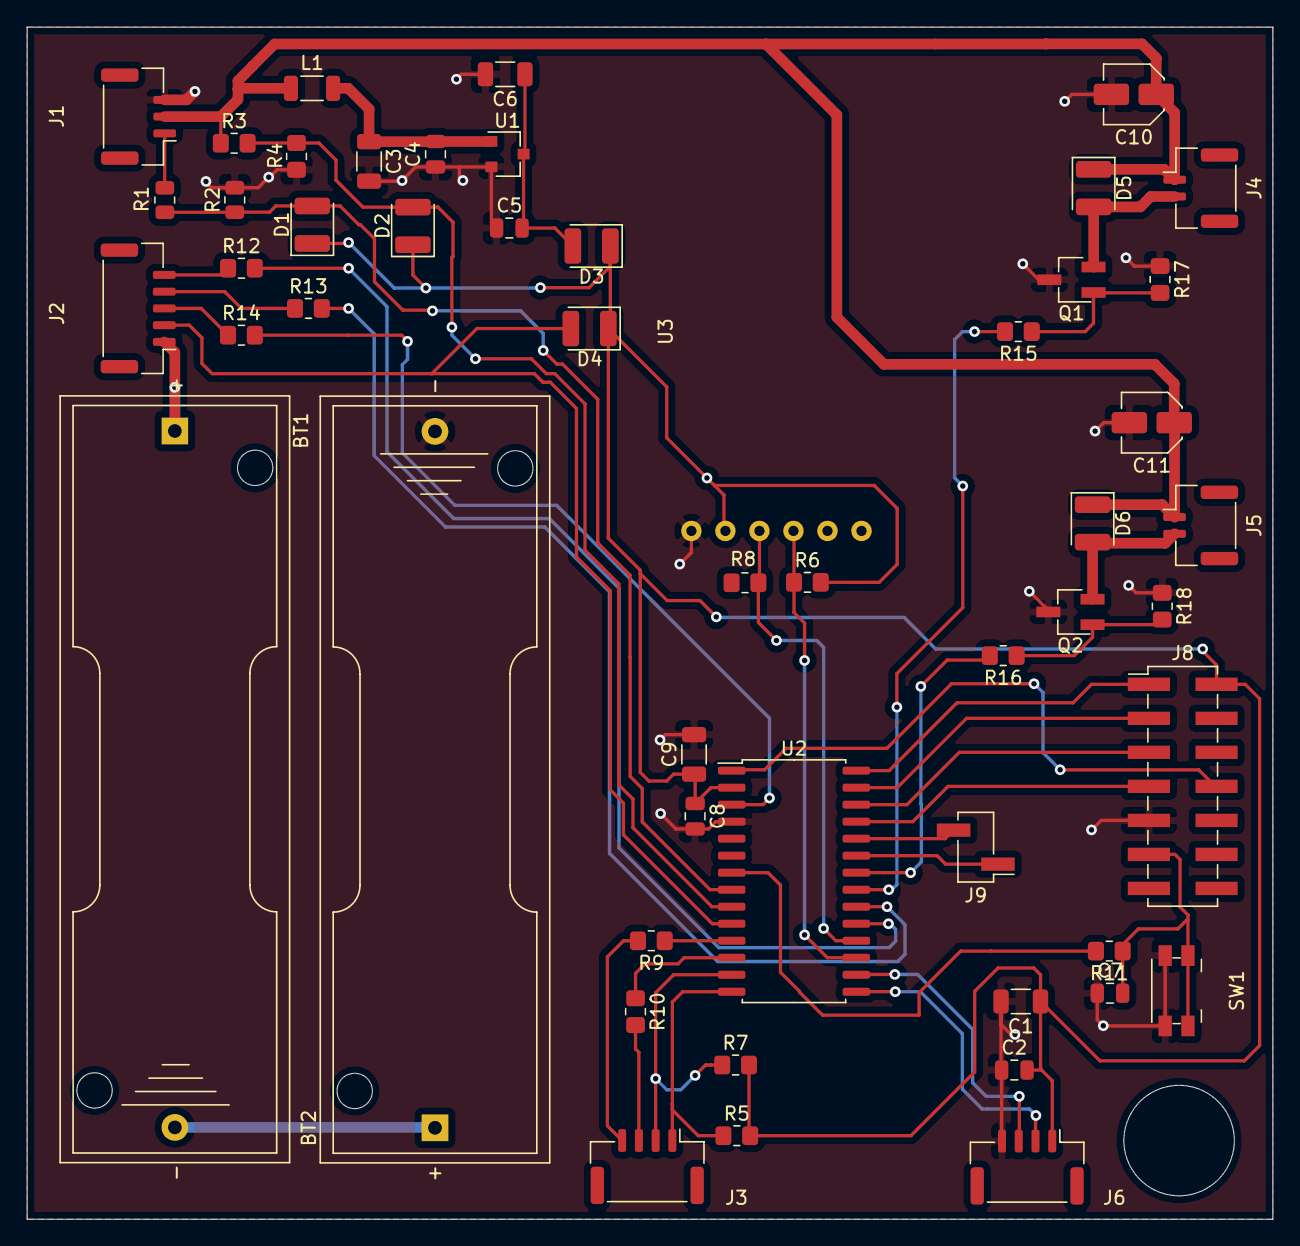
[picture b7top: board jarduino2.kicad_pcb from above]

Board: 2 copper layers, 93.0 x 89.0 mm, 52 parts (0 on the bottom side), 42 nets.
